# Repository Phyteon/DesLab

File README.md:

# DesLab
This repository contains project of digital compass/small magnetic field sensor.

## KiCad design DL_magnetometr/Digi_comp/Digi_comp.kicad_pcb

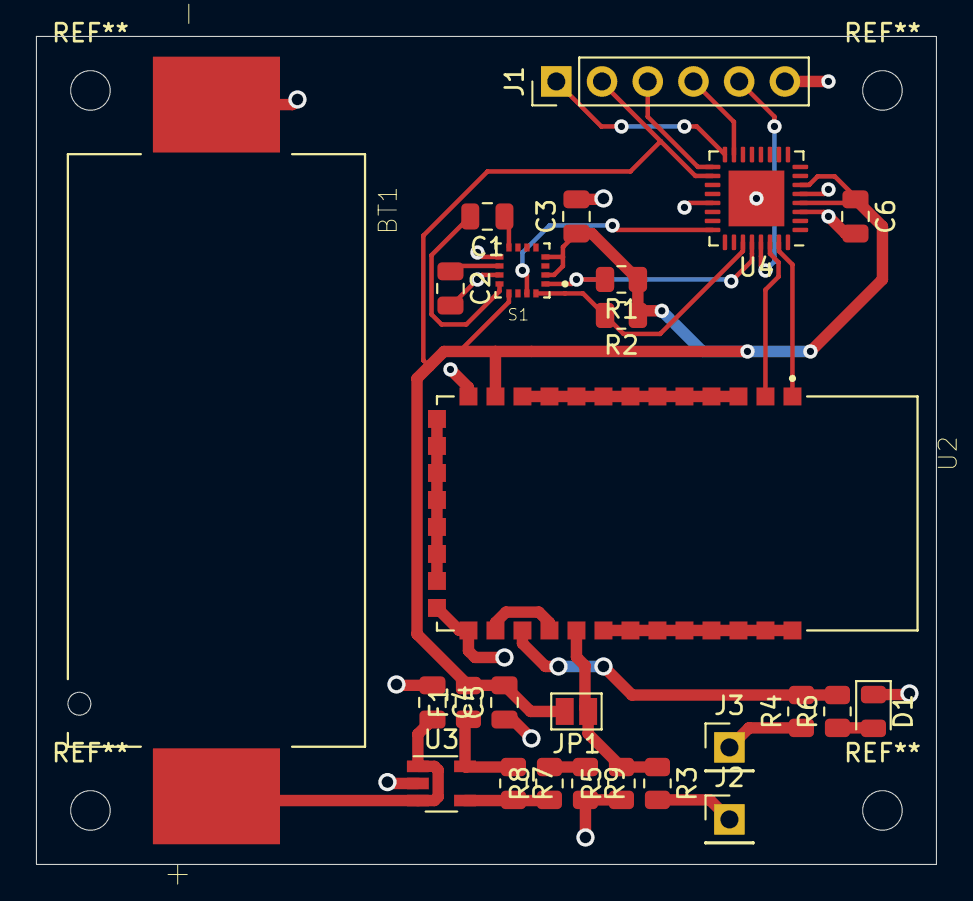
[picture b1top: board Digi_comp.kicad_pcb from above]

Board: 2 copper layers, 50.0 x 46.0 mm, 26 parts (0 on the bottom side), 23 nets.

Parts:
BT1: Battery_Cell; 2AA-SM
C1: 220n; C_0805_2012Metric
C2: 4.7u; C_0805_2012Metric
C3, C6: 100n; C_0805_2012Metric
C4, C5: 1u; C_0805_2012Metric
D1: LED; D_0805_2012Metric
F1: Fuse_Small; Fuse_0805_2012Metric
J1: Conn_01x06_Male; PinHeader_1x06_P2.54mm_Vertical
J2, J3: Conn_01x01_Male; PinHeader_1x01_P2.54mm_Vertical
JP1: Jumper; SolderJumper-2_P1.3mm_Open_Pad1.0x1.5mm
R1, R2: 2.2k; R_0805_2012Metric
R3, R4, R6: 470; R_0805_2012Metric
R5, R7: 10k; R_0805_2012Metric
R8: 22.6k; R_0805_2012Metric
R9: 49.9k; R_0805_2012Metric
S1: HMC5883L; XDCR_HMC5883L-TR
U2: HC-06; XCVR_BLUETOOTH-SERIAL-HC-06
U3: AP7331-WG-7; TSOT-23-5
U4: ATmega328P-MU; QFN-32-1EP_5x5mm_P0.5mm_EP3.1x3.1mm

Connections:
3.3V: C3.1, C5.2, C6.1, F1.2, J1.2, JP1.2, R1.1, R2.1, S1.2, S1.4, S1.13, U2.12, U4.4, U4.6, U4.18
3.6V: BT1.P, C4.2, U3.1, U3.3
GND: BT1.N, C2.2, C3.2, C4.1, C5.1, C6.2, D1.1, J1.6, R5.1, R9.2, S1.9, S1.11, U2.13, U2.21, U2.22, U3.2, U4.3, U4.5, U4.21, U4.33
INT: S1.15, U4.24
unnamed: C1.1, S1.8
unnamed: C1.2, S1.12
unnamed: C2.1, S1.10
unnamed: D1.2, R6.1
unnamed: F1.1, R7.1, U3.5
unnamed: J1.1, U4.16
unnamed: J1.3, U4.17
unnamed: J1.4, U4.15
unnamed: J1.5, U4.29
unnamed: J2.1, R3.2
unnamed: J3.1, R4.1
unnamed: JP1.1, R3.1, R5.2, U2.26
unnamed: R4.2, R6.2, U2.24
unnamed: R7.2, R8.1, U3.4
unnamed: R8.2, R9.1
SCL: R1.2, S1.1, U4.28
SDA: R2.2, S1.16, U4.27
UART_RXD: U2.2, U4.30
UART_TXD: U2.1, U4.31

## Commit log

2020-12-13 Added base files and documentation
2020-12-14 Modified scheme
    Now utilising on-chip DC-DC converter for lower power consumption. Added overcurrent protection fuses.
2020-12-15 Added new symbol
    Added symbol of the PK20DX128VFM5 component (required for programming the MCU)
2020-12-15 Added ESD protection circuitry
2020-12-15 Added #TODO comments
2020-12-15 Prototype of programming unit added
2020-12-16 Estetic changes
2020-12-17 Added descriptions and changed placement for readability.
2020-12-17 Added documentation in LaTeX - version 2.0
2020-12-18 Added comments.
2020-12-22 Added new bluetooth module, but not erased the old one
2020-12-28 Deleted unused modules, changed buffer to Schottky diode
2021-01-13 Added AtMega328P
2021-01-13 Added connections to sensor.
2021-01-14 Added more info to documentation
2021-01-21 Added some footprints, started layout
2021-01-23 Changed power supply to battery.
2021-01-23 Layout continuation
2021-01-24 Layout finished
2021-01-24 Exit save
